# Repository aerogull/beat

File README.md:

# beat - a mouse designed for any case
I've wanted to design my own mouse for the longest time. I've built my own keyboard, so it was just the next logical step, right? Well, the complexity from a keyboard run off a microcontroller powered by qmk, to a custom programmed mouse with a proprietary mouse sensor and a nRF52 chip, was quite the leap. This is a v1, it's not going to be light, it's not going to be very small, the side button connectors will likely be changed, and the case will not be ergonomic in any way that isn't comfortable to me. The firmware will be slower than most modern mice, and I probably won't be able to bring out the full speed of the PAW3395 sensor used (if I use ESB). But this is a testing board, and changes will be made to improve it in the future! With that, onto the specs and design!
## PCB
- nRF52840
- PAW3395
- 11mm compatible Alps scroll (w middle click)
- 4 Omron Switches (1 other switch for middle click)
- Lipo battery (500mAH)
- Dongle (nRF52840 + USBC) (COMING SOON)
- USBC charging

## Case
It's just a simple design without great ergonomics, mostly used for testing and ease of access to the board.
## Firmware
_**Warning: The PAW3395 Driver is Propiretiary, and Can Not Be Provided by Me**_ 

## BOM
|Reference|Qty|Value|DNP|Exclude from BOM|Exclude from Board|Footprint|Datasheet|
|-----|-----|-----|-----|-----|-----|-----|-----|
|A1|1|~||||custom:PAW3395||
|C1,C29,C39|	3|	4.7μF|	|	|	|	Capacitor_SMD:C_0805_2012Metric_Pad1.18x1.45mm_HandSolder|	~|
|C2,C4,C5,C13,C14,C19,C20,C21,C22,C23,C28,C31,C38|	13|	100nF|	|	|	|	Capacitor_SMD:C_0805_2012Metric_Pad1.18x1.45mm_HandSolder|	~|
|C3,C6,C8,C10,C12,C15,C16,C18,C41,C43|	10|	10μF|	|	|	|	Capacitor_SMD:C_0805_2012Metric_Pad1.18x1.45mm_HandSolder|	~|
|C7|	1|	33uF|	|	|	|	Capacitor_SMD:C_0805_2012Metric_Pad1.18x1.45mm_HandSolder|	~|
|C11,C17,C42|	3|	1μF|	|	|	|	Capacitor_SMD:C_0805_2012Metric_Pad1.18x1.45mm_HandSolder|	~|
|C24,C25,C26,C27|	4|	12pF|	|	|	|	Capacitor_SMD:C_0805_2012Metric_Pad1.18x1.45mm_HandSolder|	~|
|C30,C32|	2|	1.0μF|	|	|	|	Capacitor_SMD:C_0805_2012Metric_Pad1.18x1.45mm_HandSolder|	~|
|C33,C37|	2|	N.C.|	|	|	|	Capacitor_SMD:C_0805_2012Metric_Pad1.18x1.45mm_HandSolder|	~|
|C34|	1|	100pF|	|	|	|	Capacitor_SMD:C_0805_2012Metric_Pad1.18x1.45mm_HandSolder|	~|
|C35|	1|	0.8pF|	|	|	|	Capacitor_SMD:C_0805_2012Metric_Pad1.18x1.45mm_HandSolder|	~|
|C36|	1|	0.5pF|	|	|	|	Capacitor_SMD:C_0805_2012Metric_Pad1.18x1.45mm_HandSolder|	~|
|D3,D5|	2|	MBR1020VL|	|	|	|	Diode_SMD:D_SOD-123F|	https://www.onsemi.com/pub/Collateral/MBR1020VL-D.PDF|
|J2|	1|	JSTPH|	|	|	|	custom:JSTPH2PINSMTRIGHTANGLECONNECTOR|	~|
|J3|	1|	USB_C_Receptacle_USB2.0_14P|	|	|	|	Connector_USB:USB_C_Receptacle_Amphenol_12401548E4-2A|	https://www.usb.org/sites/default/files/documents/usb_type-c.zip|
|L1,L4|	2|	10μH|	|	|	|	Inductor_SMD:L_0805_2012Metric_Pad1.05x1.20mm_HandSolder|	~|
|L2|	1|	15nH|	|	|	|	Inductor_SMD:L_0805_2012Metric_Pad1.05x1.20mm_HandSolder|	~|
|L3|	1|	3.3nH|	|	|	|	Inductor_SMD:L_0805_2012Metric_Pad1.05x1.20mm_HandSolder|	~|
|LED1|	1|	SK6812MINI-E|	|	|	|	custom:SK6812MINIE|	http://yushakobo.jp/ds/YS-SK6812MINI-E.pdf|
|R1,R9,R10,R11,R12,R13,R20,R21|	8|	10kΩ|	|	|	|	Resistor_SMD:R_0805_2012Metric_Pad1.20x1.40mm_HandSolder|	~|
|R2|	1|	5.6Ω|	|	|	|	Resistor_SMD:R_0805_2012Metric_Pad1.20x1.40mm_HandSolder|	~|
|R3|	1|	2kΩ|	|	|	|	Resistor_SMD:R_0805_2012Metric_Pad1.20x1.40mm_HandSolder|	~|
|R4,R5,R8|	3|	100kΩ|	|	|	|	Resistor_SMD:R_0805_2012Metric_Pad1.20x1.40mm_HandSolder|	~|
|R6|	1|	5.1kΩ|	|	|	|	Resistor_SMD:R_0805_2012Metric_Pad1.20x1.40mm_HandSolder|	~|
|SW1,SW2,SW4,SW5|	4|	SW_SPST|	|	|	|	custom:SW_Tactile_SPDT_Omron_D2F|	~|
|SW3|	1|	SW_SPST|	|	|	|	Button_Switch_THT:SW_PUSH_6mm|	~|
|SW6,SW7|	2|	SW_SPST|	|	|	|	Capacitor_SMD:C_0402_1005Metric|	~|
|SW8|	1|	RotaryEncoder|	|	|	|	custom:EC10E1220503|	~|
|SW9|	1|	SW_SPST|	|	|	|	Button_Switch_SMD:SW_SPST_CK_RS282G05A3|	~|
|U2|	1|	SPX3819M5-L-3-3|	|	|	|	Package_TO_SOT_SMD:SOT-23-5|	https://www.exar.com/content/document.ashx?id=22106&languageid=1033&type=Datasheet&partnumber=SPX3819&filename=SPX3819.pdf&part=SPX3819|
|U3|	1|	MCP73831-2-OT|	|	|	|	Package_TO_SOT_SMD:SOT-23-5|	http://ww1.microchip.com/downloads/en/DeviceDoc/20001984g.pdf|
|U4|	1|	TLV70019_SOT23-5|	|	|	|	Package_TO_SOT_SMD:SOT-23-5|	http://www.ti.com/lit/ds/symlink/tlv700.pdf|
|U5|	1|	nRF52840|	|	|	|	Package_DFN_QFN:Nordic_AQFN-73-1EP_7x7mm_P0.5mm|	http://infocenter.nordicsemi.com/topic/com.nordic.infocenter.nrf52/dita/nrf52/chips/nrf52840.html|
|U6|	1|	SPX3819M5-L-5-0|	|	|	|	Package_TO_SOT_SMD:SOT-23-5|	https://www.exar.com/content/document.ashx?id=22106&languageid=1033&type=Datasheet&partnumber=SPX3819&filename=SPX3819.pdf&part=SPX3819|
|Y1|	1|	32.768 Hz|	|	|	|	custom:FC135327680KAA|	~|
|Y2|	1|	32 Hz|	|	|	|	custom:ABM8A32000MHZD2YT3|	~|

part sources for my use:

https://www.aliexpress.us/item/3256808047644394.html\
https://www.aliexpress.us/item/2251832785225269.html\
https://www.aliexpress.us/item/3256808439402083.html\
https://www.aliexpress.us/item/3256808650485013.html\
https://www.aliexpress.us/item/3256808865384672.html\
https://www.aliexpress.us/item/3256809185954100.html

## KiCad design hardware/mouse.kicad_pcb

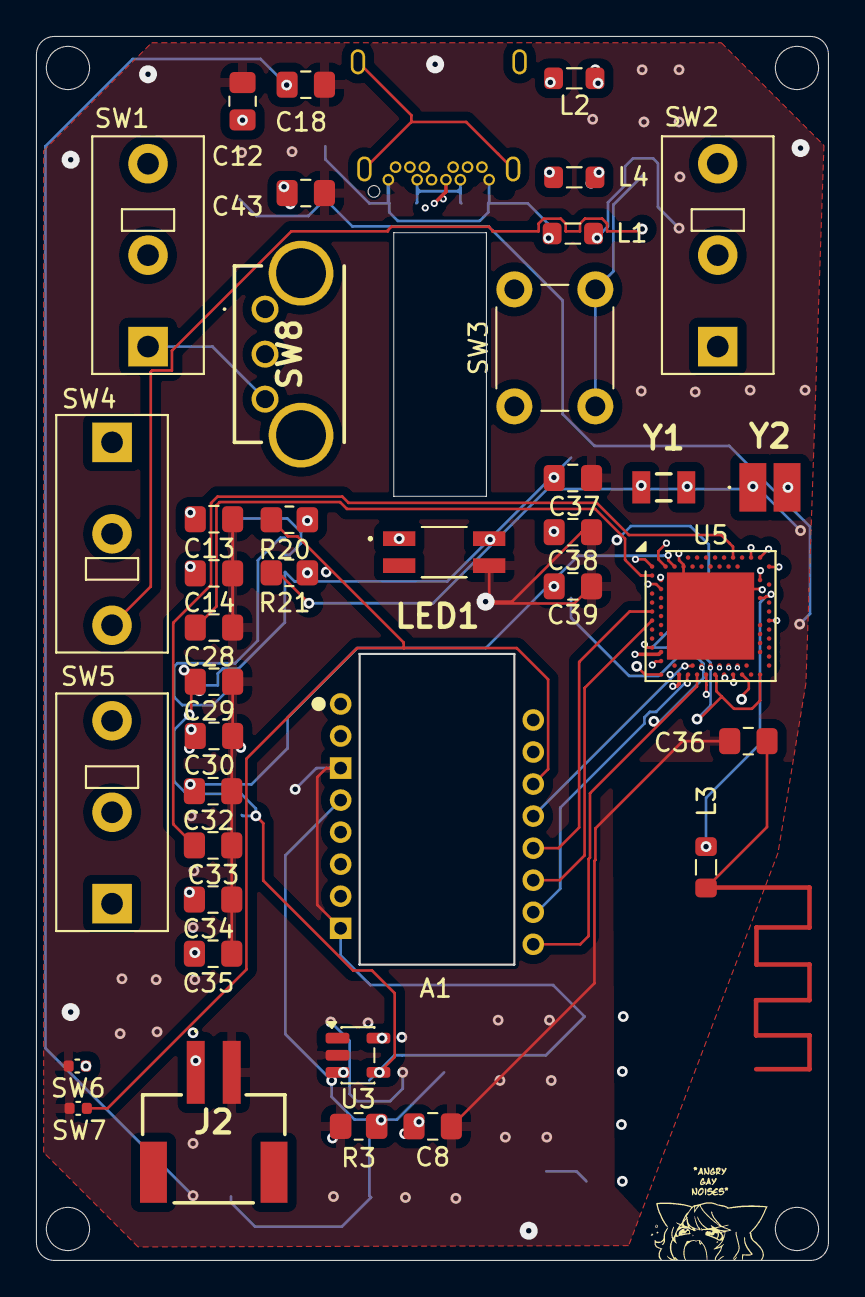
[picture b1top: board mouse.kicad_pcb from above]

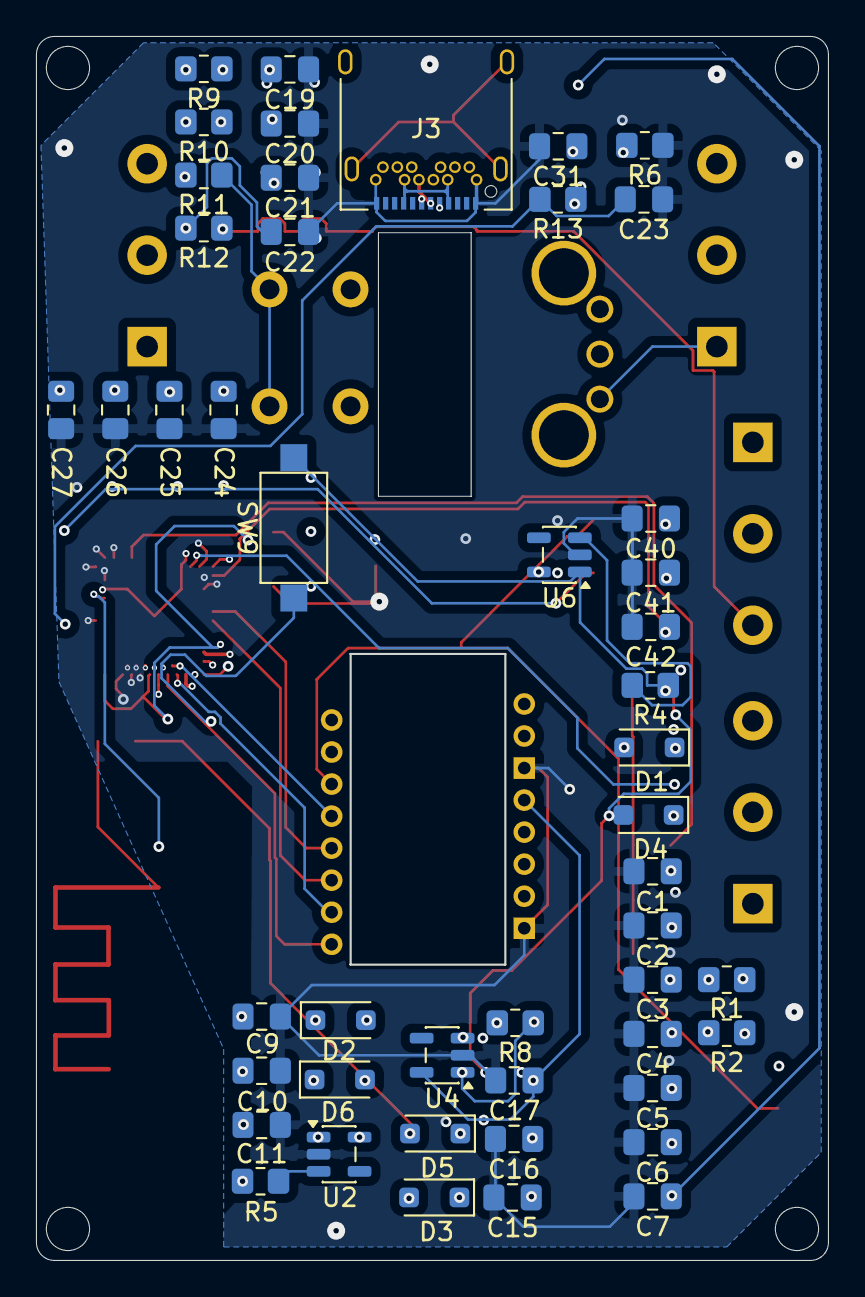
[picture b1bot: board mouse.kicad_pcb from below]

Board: 4 copper layers, 43.9 x 67.9 mm, 87 parts (48 on the bottom side), 55 nets.

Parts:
A1: PAW3395
C1: 4.7uF; C_0805_2012Metric_Pad1.18x1.45mm_HandSolder
C2, C4, C5, C13, C14, C19, C20, C21, C22, C23, C28, C31, C38: 100nF; C_0805_2012Metric_Pad1.18x1.45mm_HandSolder
C3, C6, C8, C9, C10, C12, C15, C16, C18, C40, C41, C43: 10uF; C_0805_2012Metric_Pad1.18x1.45mm_HandSolder
C7: 33uF; C_0805_2012Metric_Pad1.18x1.45mm_HandSolder
C11, C17, C42: 1uF; C_0805_2012Metric_Pad1.18x1.45mm_HandSolder
C24, C25, C26, C27: 12pF; C_0805_2012Metric_Pad1.18x1.45mm_HandSolder
C29, C39: 4.7μF; C_0805_2012Metric_Pad1.18x1.45mm_HandSolder
C30, C32: 1.0μF; C_0805_2012Metric_Pad1.18x1.45mm_HandSolder
C33, C37: N.C.; C_0805_2012Metric_Pad1.18x1.45mm_HandSolder
C34: 100pF; C_0805_2012Metric_Pad1.18x1.45mm_HandSolder
C35: 0.8pF; C_0805_2012Metric_Pad1.18x1.45mm_HandSolder
C36: 0.5pF; C_0805_2012Metric_Pad1.18x1.45mm_HandSolder
D1, D2, D3, D4, D5, D6: MBR1020VL; D_SOD-123F
J2: JSTPH; JSTPH2PINSMTRIGHTANGLECONNECTOR
J3: USB_C_Receptacle_USB2.0_14P; USB_C_Receptacle_Amphenol_12401548E4-2A
L1, L4: 10μH; L_0805_2012Metric_Pad1.05x1.20mm_HandSolder
L2: 15nH; L_0805_2012Metric_Pad1.05x1.20mm_HandSolder
L3: 3.3nH; L_0805_2012Metric_Pad1.05x1.20mm_HandSolder
LED1: SK6812MINI-E; SK6812MINIE
R1, R9, R10, R11, R12, R13, R20, R21: 10kΩ; R_0805_2012Metric_Pad1.20x1.40mm_HandSolder
R2: 5.6Ω; R_0805_2012Metric_Pad1.20x1.40mm_HandSolder
R3: 2kΩ; R_0805_2012Metric_Pad1.20x1.40mm_HandSolder
R4, R5, R8: 100kΩ; R_0805_2012Metric_Pad1.20x1.40mm_HandSolder
R6: 5.1kΩ; R_0805_2012Metric_Pad1.20x1.40mm_HandSolder
SW1, SW2, SW4, SW5: SW_SPST; SW_Tactile_SPDT_Omron_D2F
SW3: SW_SPST; SW_PUSH_6mm
SW6, SW7: SW_SPST; C_0402_1005Metric
SW8: RotaryEncoder; EC10E1220503
SW9: SW_SPST; SW_SPST_CK_RS282G05A3
U2: SPX3819M5-L-3-3; SOT-23-5
U3: MCP73831-2-OT; SOT-23-5
U4: TLV70019_SOT23-5; SOT-23-5
U5: nRF52840; Nordic_AQFN-73-1EP_7x7mm_P0.5mm
U6: SPX3819M5-L-5-0; SOT-23-5
Y1: 32.768 Hz; FC135327680KAA
Y2: 32 Hz; ABM8A32000MHZD2YT3

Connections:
+3.3V: A1.7 (VDDIO), C3.1, C4.1, C10.1, C11.1, C12.1, R1.1, R20.2, R21.2, SW1.1 (A), SW2.1 (A), SW3.1 (A), SW4.1 (A), SW5.1 (A), SW8.C, U2.5 (OUT)
+5V: C41.1, C42.1, C43.1, LED1.1 (VDD), U6.5 (OUT)
+BATT: C8.1, C39.1, D1.2 (A), D2.2 (A), D3.2 (A), J2.1, U3.3 (V_{BAT}), U5.Y2 (VDDH)
C1-1: C24.2, U5.D2 (XL1/P0.00), Y1.1
C1-2: C25.2, U5.F2 (XL2/P0.01), Y1.2
C2-1: C26.2, U5.A23 (XC2), Y2.1
C2-2: C27.2, U5.B24 (XC1), Y2.2
D+: J3.A6 (D+), J3.B6 (D+), U5.AD6 (D+)
D-: J3.A7 (D-), J3.B7 (D-), U5.AD4 (D-)
DCCH: L4.2, U5.AB2 (DCCH)
GND: A1.3 (GND), A1.8 (GNDIO), C1.2, C2.2, C3.2, C4.2, C5.2, C6.2, C7.2, C8.2, C9.2, C10.2, C11.2, C12.2, C13.2, C14.2, C15.2, C16.2, C17.2, C18.2, C19.1, C20.1, C21.1, C22.1, C23.1, C24.1, C25.1, C26.1, C27.1, C28.2, C29.2, C30.2, C31.2, C32.2, C33.2, C34.2, C35.2, C36.2, C37.2, C38.2, C39.2, C40.2, C41.2, C42.2, C43.2, J2.2, J3.A1 (GND), J3.A12 (GND), J3.B1 (GND), J3.B12 (GND), LED1.3 (GND), R3.1, R6.1, SW6.1 (A), SW7.1 (A), U2.2 (GND), U3.2 (V_{SS}), U4.2 (GND), U5.B7 (VSS), U5.EP (VSS), U5.F23 (VSS_PA), U6.2 (GND)
LED: LED1.4 (DIN), U5.AD20 (P0.24)
MISO: A1.12 (MISO), U5.L1 (P0.06)
MOSI: A1.11 (MOSI), R1.2, U5.N1 (P0.08)
MOTION: A1.9 (MOTION), U5.AD10 (P0.15)
MSNCS: A1.13 (NCS), U5.AC9 (P0.14)
NRESET: A1.14 (NRESET), R20.1, SW7.2 (B)
unnamed: A1.15 (LED_P), R2.2
unnamed: A1.5 (VDDREG), C1.1, C2.1
unnamed: C36.1, L3.2
unnamed: C40.1, D1.1 (K), D4.1 (K)
unnamed: C9.1, D2.1 (K), D6.1 (K)
unnamed: D3.1 (K), D5.1 (K), SW9.1 (A)
unnamed: J3.A5 (CC1), J3.B5 (CC2), R6.2
unnamed: C31.1, J3.S1 (SHIELD)
unnamed: L1.2, L2.1
unnamed: R9.1, SW1.2 (B)
unnamed: R10.1, SW2.2 (B)
unnamed: R11.1, SW3.2 (B)
unnamed: R12.1, SW4.2 (B)
unnamed: R13.1, SW5.2 (B)
unnamed: C15.1, R4.1, R5.1, R8.1, SW9.2 (B), U2.1 (IN), U4.1 (IN), U6.1 (IN)
unnamed: R5.2, U2.3 (EN)
unnamed: R3.2, U3.5 (PROG)
unnamed: R8.2, U4.3 (EN)
unnamed: C28.1, U5.C1 (DEC1)
unnamed: C33.1, U5.A18 (DEC2)
unnamed: C34.1, U5.D23 (DEC3)
unnamed: C37.1, U5.N24 (DEC5)
unnamed: R4.2, U6.3 (EN)
RECCW: SW8.B, U5.AC19 (P0.23)
RECW: SW8.A, U5.AD18 (P0.22)
RESET: R21.1, SW6.2 (B), U5.AC13 (P0.18/~RESET)
RFANT: C35.1, L3.1, U5.H23 (ANT)
RFDCC: L1.1, U5.B3 (DCC)
RFDEC4: C32.1, L2.2, U5.B5 (DEC4)
SCLK: A1.10 (SCLK), U5.AD8 (P0.13)
Switch1: C19.2, R9.2, U5.AC11 (P0.16)
Switch2: C20.2, R10.2, U5.AD12 (P0.17)
Switch3: C21.2, R11.2, U5.AC15 (P0.19)
Switch4: C22.2, R12.2, U5.AD16 (P0.20)
Switch5: C23.2, R13.2, U5.AC17 (P0.21)
VBUS: C29.1, D4.2 (A), D5.2 (A), D6.2 (A), J3.A4 (VBUS), J3.A9 (VBUS), J3.B4 (VBUS), J3.B9 (VBUS), U3.4 (V_{DD}), U5.AD2 (VBUS)
VDDW1: C13.1, C14.1, C30.1, C38.1, L4.1, U5.A22 (VDD), U5.AD14 (VDD), U5.AD23 (VDD), U5.B1 (VDD), U5.W1 (VDD)
VDD_1.9V: A1.4 (VDD), C5.1, C6.1, C7.1, C16.1, C17.1, C18.1, R2.1, U4.5 (OUT)

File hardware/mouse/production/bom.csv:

Designator,Footprint,Quantity,Value,LCSC Part #
A1,PAW3395,1,~,
C1,0805,1,4.7uF,
"C10, C12, C15, C16, C18, C3, C40, C41, C43, C6, C8, C9",0805,12,10uF,
"C11, C17, C42",0805,3,1uF,
"C13, C14, C19, C2, C20, C21, C22, C23, C28, C31, C38, C4, C5",0805,13,100nF,
"C24, C25, C26, C27",0805,4,12pF,
"C29, C39",0805,2,4.7μF,
"C30, C32",0805,2,1.0μF,
C34,0805,1,100pF,
C35,0805,1,0.8pF,
C36,0805,1,0.5pF,
C7,0805,1,33uF,
"D1, D2, D3, D4, D5, D6",D_SOD-123F,6,MBR1020VL,
J2,JSTPH2PINSMTRIGHTANGLECONNECTOR,1,JSTPH,
J3,USB_C_Receptacle_Amphenol_12401548E4-2A,1,USB_C_Receptacle_USB2.0_14P,
"L1, L4",0805,2,10μH,
L2,0805,1,15nH,
L3,0805,1,3.3nH,
LED1,SK6812MINIE,1,SK6812MINI-E,
"R1, R10, R11, R12, R13, R20, R21, R9",0805,8,10kΩ,
R2,0805,1,5.6Ω,
R3,0805,1,2kΩ,
"R4, R5, R8",0805,3,100kΩ,
R6,0805,1,5.1kΩ,
"SW1, SW2, SW4, SW5",SW_Tactile_SPDT_Omron_D2F,4,SW_SPST,
SW3,SW_PUSH_6mm,1,SW_SPST,
"SW6, SW7",0402,2,SW_SPST,
SW8,EC10E1220503,1,RotaryEncoder,
SW9,SW_SPST_CK_RS282G05A3,1,SW_SPST,
U2,SOT-23-5,1,SPX3819M5-L-3-3,
U3,SOT-23-5,1,MCP73831-2-OT,
U4,SOT-23-5,1,TLV70019_SOT23-5,
U5,Nordic_AQFN-73-1EP_7x7mm_P0.5mm,1,nRF52840,
U6,SOT-23-5,1,SPX3819M5-L-5-0,
Y1,FC135327680KAA,1,32.768 Hz,
Y2,ABM8A32000MHZD2YT3,1,32 Hz,

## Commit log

2025-10-10 added 1.9v supply and 5 switches
2025-11-13 finished schem, peer review next
2025-11-27 mostly just eod stuff, a couple csv files and readme changes
2025-11-28 added case v1
2025-12-29 meow :3
2025-12-29 wowsa, thats a lot o' debugging
2026-01-01 trying to understand what jlc is doing
2026-01-06 idr what changed in this one
2026-01-07 new readme changes
2026-01-11 some changes
2026-01-16 changed README
